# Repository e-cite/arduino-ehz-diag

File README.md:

# EHZ Diagnose-Tool 1-Kanal mit Buzzer
## Aufbau und Funktionsweise
Schaltpläne, PCB und Software für ein Smart-Meter (EHZ EDL-21) Diagnose-Tool für den Arduino UNO.

Mit einem Infrarot (IR) Schreib-Lesekopf können die IR-Signale des Smart-Meters eingelesen werden.
Eine Transistorstufe bereitet die Signale auf und invertiert diese, um als RX-Signal vom Arduino
verarbeitet zu werden. Per TX können eigene Signale gesendet werden, was in der Regel jedoch nur
selten benötigt wird.

Ein Piezo Buzzer ermöglicht die Ausgabe von Diagnose-Tönen.

Die Platine kann als Arduino-Shield verwendet werden. In Kombination mit einem SD-Karten oder
Ethernet-Shield können die gelesenen Daten auf SD-Karte gespeichert oder per Ethernet versendet
werden.

## Software
Die Schaltpläne sind mit KiCAD (https://www.kicad.org/) erstellt.

Als IDE kommt die Arduino IDE (https://www.arduino.cc/en/software/) zum Einsatz.

## Hardware
Die Abmessungen des Sensors sind nachfolgend dargestellt.

## Verwandete Projekte
- eHZy (https://sourceforge.net/projects/ehzy/)
- Volkszaehler (https://wiki.volkszaehler.org/hardware/controllers/ir-schreib-lesekopf-ttl-ausgang)

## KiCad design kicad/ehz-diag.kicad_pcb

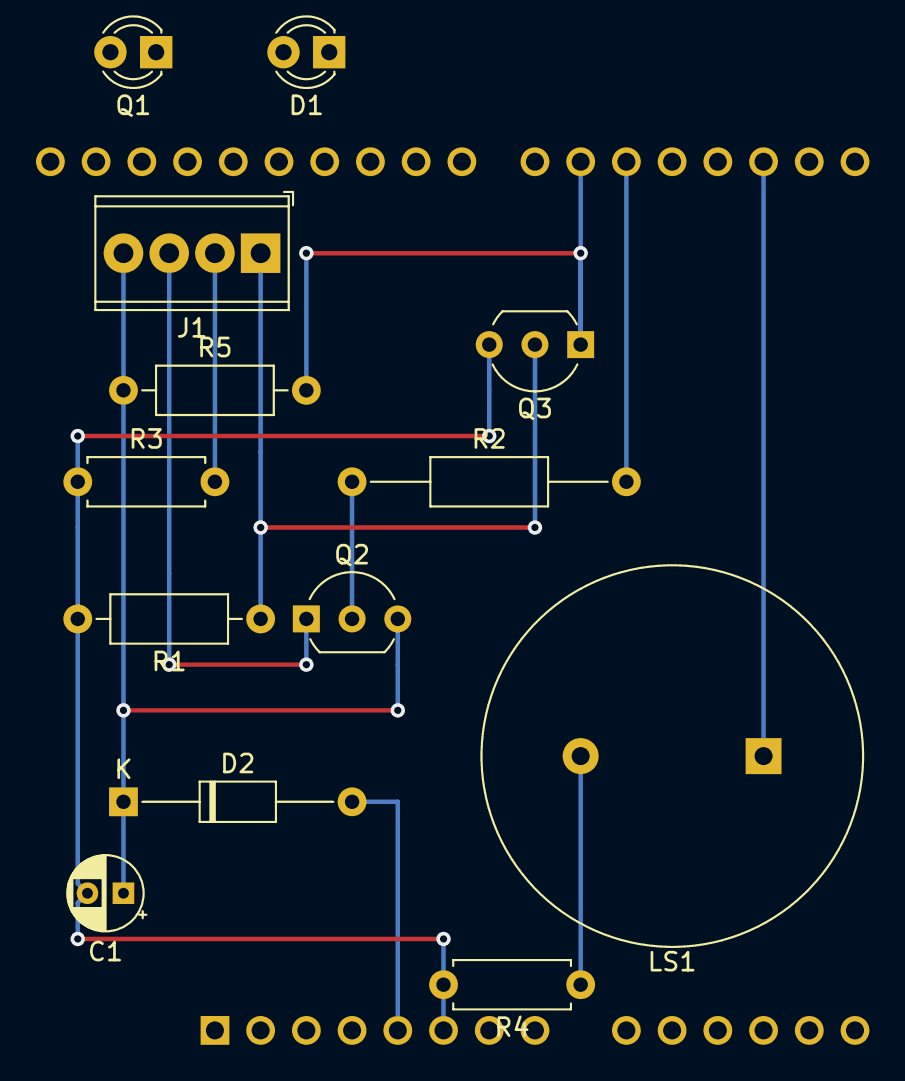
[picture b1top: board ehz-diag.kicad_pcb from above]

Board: 2 copper layers, 14 parts (1 on the bottom side), 11 nets.

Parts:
A1: Arduino_UNO_R3
C1: 1µ; CP_Radial_D4.0mm_P2.00mm
D1: L-934SF4C; LED_D3.0mm_IRBlack
D2: BAT46; D_DO-35_SOD27_P12.70mm_Horizontal
J1: Screw-Terminal; TerminalBlock_Phoenix_MPT-0,5-4-2.54_1x04_P2.54mm_Horizontal
LS1: Piezo Buzzer; Buzzer_22x7.5RM7.6
Q1: SFH309FA; LED_D3.0mm_Clear
Q2: BC557; TO-92_Inline_Wide
Q3: BC548; TO-92_Inline_Wide
R1, R5: 10k; R_Axial_DIN0207_L6.3mm_D2.5mm_P10.16mm_Horizontal
R2: 10k; R_Axial_DIN0207_L6.3mm_D2.5mm_P15.24mm_Horizontal
R3, R4: 220; R_Axial_DIN0207_L6.3mm_D2.5mm_P7.62mm_Horizontal

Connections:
+5V: C1.1, D2.1, J1.4, Q2.3, R5.1
/RXD1: A1.21, Q3.1, R5.2
/TXD1: A1.20, R2.2
GND: A1.6, C1.2, Q3.3, R1.2, R3.1, R4.2
unnamed: A1.5, D2.2
unnamed: A1.17, LS1.1
unnamed: J1.1, Q3.2, R1.1
unnamed: J1.2, R3.2
unnamed: J1.3, Q2.1
unnamed: LS1.2, R4.1
unnamed: Q2.2, R2.1

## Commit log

2021-08-30 Initiale Version der Schaltpläne und des PCB hinzugefügt.
2021-08-30 README.md aktualisiert und Abmessungen des Sensors hinzugefügt.
2021-09-05 Issue #1: Schaltplan Rev. 1.1
    - J1: Farben in Beschriftung korrigiert
    - R2: Beschriftung gedreht
2021-09-15 Arduino-Sketch zur Diagnose hinzugefügt.
    Kann folgende Parameter auslesen:
    - Geräteidentifikation
    - Wirkleistung
    - Zählerstand
